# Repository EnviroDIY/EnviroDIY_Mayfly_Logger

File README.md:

EnviroDIY Mayfly Data Logger
==============
The [EnviroDIY™ Mayfly Data Logger](http://envirodiy.org/mayfly/) is an Arduino-framework microcontroller board designed specifically for environmental Internet of Things (IoT) applications with the goal to facilitate professional-quality, do-it-yourself (DIY) environmental science and monitoring.

This [EnviroDIY_Mayfly_Logger Github repository](https://github.com/EnviroDIY/EnviroDIY_Mayfly_Logger) provides hardware design files and example code sketches, the [EnviroDIY community](https://www.envirodiy.org) provides support via project posts and forums, and the [Mayfly Logger board is available for purchase on the [EnviroDIY Shop](https://www.envirodiy.org/shop/) for user convenience.

## Features:

- ATmega1284p processor
    - 128kB program (flash) memory, 16kB RAM
    - 2 UART, 1 I2C, 1 SPI connection
    - 32 total I/O pins
    - 3.3V, 8MHz operating frequency
- Integrated 6V solar lipo battery charger
- Precise real time clock (RTC, [DS3231](https://datasheets.maximintegrated.com/en/ds/DS3231.pdf)) with separate power supply
- Auxillary 16 bit ADC ([TI ADS1115](http://www.ti.com/lit/ds/symlink/ads1114.pdf))
- FTDI chip for USB communication via USB-C port
- microSD memory card socket
- XBee radio/wifi/cellular module socket
- 7 [Grove](http://wiki.seeedstudio.com/Grove_System/) connectors with access to I2C, auxillary ADC, and digital pins
- 0.5A switchable power supply for sensors at 3.3V and 5V, and 0.15A at 12V
- On-board power switch
- Two controllable LED's (red and green)
- One programmable push-button
- Onboard humidity/temperature sensor and analog light sensor
- Onboard auxiliary 8MB flash memory chip

## Pin-out for v1.x

| Pin Number[s] | Function             | Access                                 | Notes |
|---------------|----------------------|----------------------------------------|-------|
| D0/D1         | Serial Rx/Tx (UART)  | Connected to FTDI for USB programming  | Also accessible via programming port, 20 pin header, and XBee socket via SJ8/9 |
| D2/D3         | Serial1 Rx/Tx (UART) | XBee socket Din/Dout (pins 2/3)        | Also accessible via 20 pin header, can be disconnected from XBee socket via SJ8/9 |
| D19           | XBee CTS             | XBee socket CTS (pin 12)               | Also accessible via 20 pin header |
| D20           | XBee RTS             | XBee socket RTS (pin 16)               | Also accessible via 20 pin header |
| D23           | XBee DTR             | XBee socket DTR (pin 9)                | Also accessible via 20 pin header |
| A5=D29*       | XBee Assoc or RI     | XBee socket Assoc or RI (pin 15 or 20) | Not connected to XBee socket by default, use SJ7 to connect; Also accessible via 20 pin header |
| D16/D17       | I2C SCL/SDA ("Wire") | Grove connector                        | Also accessible via 20 pin header |
| D13/D14/D15   | SPI MOSI/MISO/SCK    | microSD card slot & SPI header         |  |
| D12           | microSD chip select  | microSD card slot & SPI header         |  |
| D18           | SD card detect OR RTC 32KHz | 20 pin header                   | Not connected to either SD or RTC by default, use SJ6 for RTC or SJ10 for SD, _do not use both_ |
| A7=D31 _or_ D10 | RTC Interrupt      | 20 pin header                          | A7 is connected to RTC interrupt by default; Use SJ1 to disconnect A7 and/or to connect D10 |
| D22           | Switched power/LED4  | Switched power on all Grove ports      | Pin is not directly accessible, only switched power; Cut SJ3 to disconnect LED4 (red) |
| D21           | user push button     | 20 pin header                          | Cut SJ to disconnect button |
| D8            | LED1 (green)         | 20 pin header                          |  |
| D9            | LED2 (red)           | 20 pin header                          |  |
| A6=D30        | Battery measurement  | None                                   | Connected via voltage divider |
| D4-7, D10-11  | General Purpose I/O  | Grove connector; 20 pin header         |  |
| AA0-AA3       | Auxilliary ADC       | Grove connector; 20 pin header         | Connected to _Auxillary_ adc (TI ADS1115), not to Mayfly analog pins |

## Solder Jumper Connections for v1.x

| Number | Function                        | Default Connection                |
|--------|---------------------------------|-----------------------------------|
| SJ1    | Connect to interrupt from RTC   | Pin A7 connected to RTC interrupt       |
| SJ2    | Disconnect D21 from user button | Pin D21 is connected to button (closed) |
| SJ3    | Disconnect D22 from LED3        | Pin D22 is connected to LED3 (closed)   |
| SJ4    | Disconnect LED4 from solar      | LED4 indicates solar charging status (closed) |
| SJ7    | Pin A5 to XBee ASSOC _or_ RI    | Not connected (all pads open)                 |
| SJ8    | XBee Din to TX0/TX1             | XBee Din connected to TX1                     |
| SJ9    | XBee Dout to RX0/RX1            | XBee Dout connected to RX1                    |
| SJ12   | D10 external pull-up            | D10 (INT2) is not pulled up externally (open) |

## Programming

Mayfly Data Logger can be programmed using standard Aruduino code and community libraries via the [Arduino Integrated Development Environment (IDE) software](https://www.arduino.cc/en/Main/Software) or the more powerful [PlatformIO](https://platformio.org) extensions for [Visual Studio Code](https://code.visualstudio.com/) or [Atom](https://atom.io/).

To use the Mayfly with the Arduino IDE you must add "EnviroDIY ATmega Boards" using the Tools > Board > Boards Manager as described in the [Mayfly Data Logger Software](http://envirodiy.org/mayfly/software/) post

No addition set-up is required to use the PlatformIO.
The proper enviroment settings for the Mayfly in a platformio.ini file are:

```ini
[env:mayfly]
platform = atmelavr
board = mayfly
framework = arduino
```

## Additional Resources and Links

- Read the [Getting Started With the Mayfly Data Logger](http://envirodiy.org/mayfly/) page on the EnviroDIY community website for guidance for beginners with the Mayfly, sensor station maintence, and data management.
- Make use of the [The EnviroDIY Mayfly Data l=Logger Forum](https://www.envirodiy.org/forum/mayfly-data-logger/) to ask and answer questions about the Mayfly
- Learn Mayfly basics following our [Mayfly Data Logger Software](http://envirodiy.org/mayfly/software/) post and running the example and workshop code sketches, using the Arduino IDE (from File > Sketchbook), from our [EnviroDIY_Mayfly_Logger > examples](https://github.com/EnviroDIY/EnviroDIY_Mayfly_Logger/tree/master/examples) or [EnviroDIY_Mayfly_Logger > workshop](https://github.com/EnviroDIY/EnviroDIY_Mayfly_Logger/tree/master/workshop) folders.
- Advance your capabilities to deploy solar-powered environmental monitoring stations with our [LearnEnviroDIY tutorial](https://envirodiy.github.io/LearnEnviroDIY/)
- Utilize the [ModularSensors](https://github.com/EnviroDIY/ModularSensors) code library and other [EnviroDIY libraries on GitHub](https://github.com/EnviroDIY) for datalogging built around the Mayfly
- Find and attend a training workshop for do-it-yourself environmental monitoring built around the Mayfly by contacting the Stroud Water Research Center's [citizen science outreach](https://stroudcenter.org/people/bressler/) or [education](https://stroudcenter.org/education/contact/) departments.

## Design Files & Further Documentation

We share our EnviroDIY Mayfly logger hardware design files and documentation in this repository's [Hardware Design Files](hardware) pages and [Documentation](doc) pages.

## License
Software sketches and code are released under the BSD 3-Clause License -- See [LICENSE.md](https://github.com/EnviroDIY/EnviroDIY_Mayfly_Logger/blob/master/LICENSE.md) file for details.

Documentation is licensed as [Creative Commons Attribution-ShareAlike 4.0](https://creativecommons.org/licenses/by-sa/4.0/) (CC-BY-SA) copyright.

Hardware designs shared are released, unless otherwise indicated, under the [CERN Open Hardware License 1.2](https://www.ohwr.org/projects/cernohl/wiki) (CERN_OHL).

## Credits
[EnviroDIY](http://envirodiy.org/)™ is presented by the Stroud Water Research Center, with contributions from a community of enthusiasts sharing do-it-yourself ideas for environmental science and monitoring.

[Shannon Hicks](https://github.com/s-hicks2) is the primary developer of the EnviroDIY Mayfly Data Logger hardware, with input from many [other contributors](https://github.com/EnviroDIY/EnviroDIY_Mayfly_Logger/graphs/contributors).

The Mayfly was developed based on the [SODAQ Mbili board](https://support.sodaq.com/sodaq-one/sodaq-mbili-1284p/) hardware and the [SODAQ Mbili bootloader](https://github.com/SodaqMoja/HardwareMbili) software, designed by Gregory Knauff (GKNFF).

This project has benefited from the support from the following funders:

* William Penn Foundation
* US Environmental Protection Agency (EPA)
* National Science Foundation, awards [EAR-0724971](http://www.nsf.gov/awardsearch/showAward?AWD_ID=0724971), [EAR-1331856](http://www.nsf.gov/awardsearch/showAward?AWD_ID=1331856), [ACI-1339834](http://www.nsf.gov/awardsearch/showAward?AWD_ID=1339834)
* Stroud Water Research Center endowment

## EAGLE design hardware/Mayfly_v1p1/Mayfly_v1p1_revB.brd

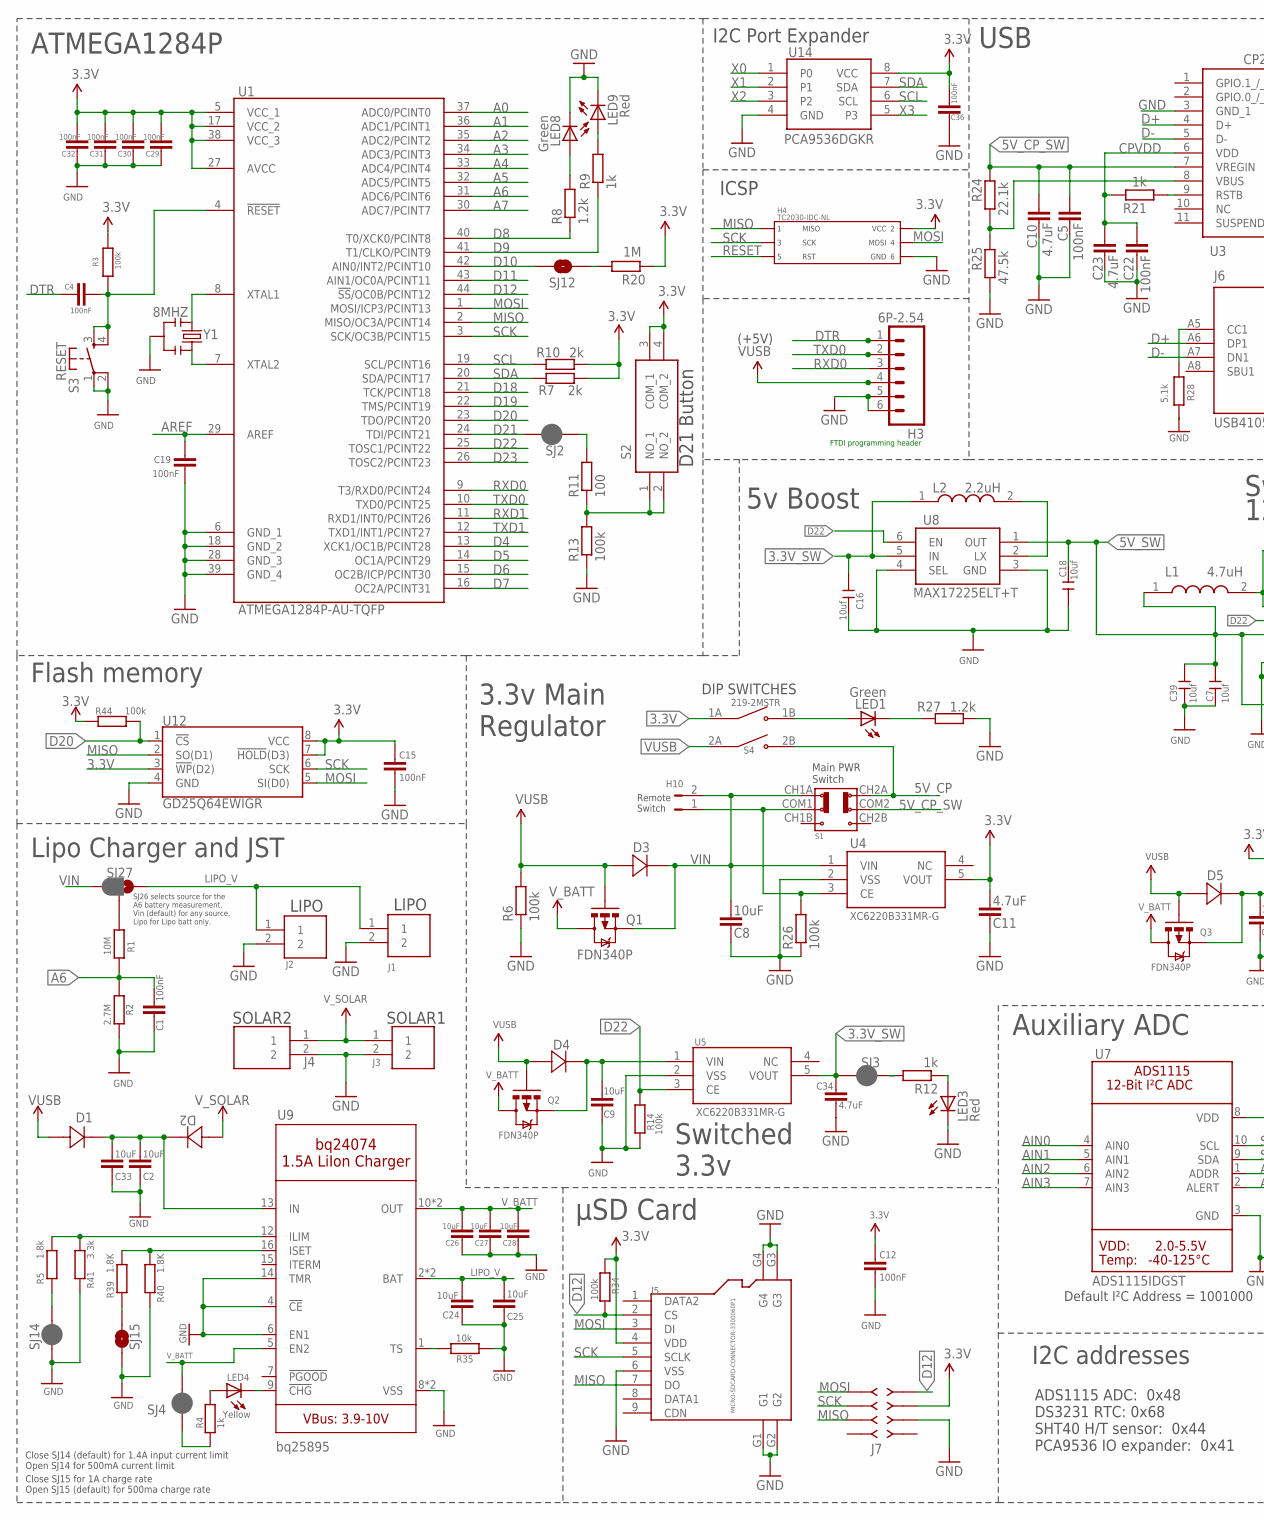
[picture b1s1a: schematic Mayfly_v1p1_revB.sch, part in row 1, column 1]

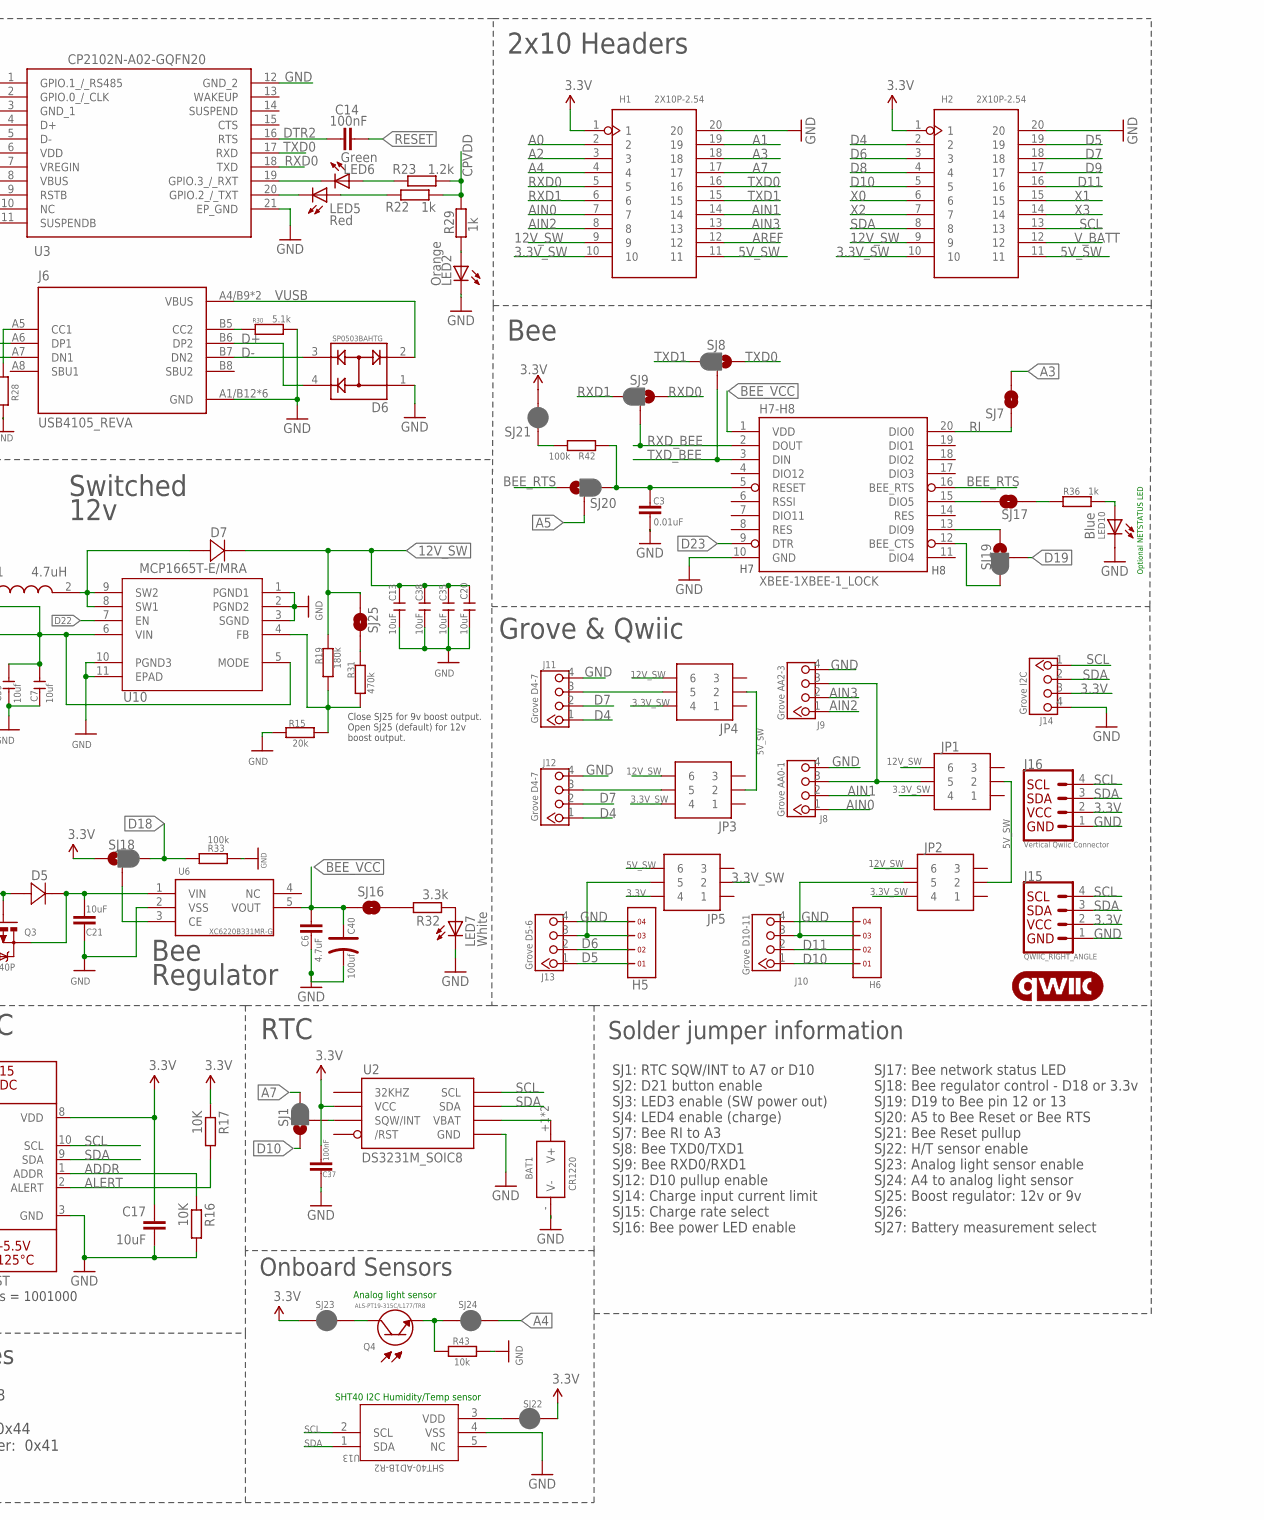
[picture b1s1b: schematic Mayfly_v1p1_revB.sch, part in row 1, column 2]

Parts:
BAT1: CR1220; BAT2P-13.5-CR1220
C1, C4, C5, C12, C14, C22, C29, C30, C31, C32, C36, C37: 100nF; C0603
C2, C8, C9, C17, C21, C24, C25, C26, C27, C28, C33: 10uF; C0603
C3: 0.01uF; C0603
C6, C10, C11, C23, C34: 4.7uF; C0603
C7, C39: 10uf; C0805
C13, C20, C35, C38: 10uF; C1206
C15, C19: 100nF; C0402
C16, C18: 10uf; C0603
C40: 100uf; AVX-B
D1, D2, D3, D4, D5, D7: MSS2P2-M3/89A; DIODE_MSP3V3
D6: SP0503BAHTG; SOT143
H1, H2: 2X10P-2.54; H2X10-2.54
H3: 6P-2.54; 1X06_FEMALE_LOCK.010
H4: TC2030-IDC-NL
H5, H6: 1X4
H7-H8: XBEE-1XBEE-1_LOCK; XBEE-1_LOCK
H10: JUMPER-PTH-2-NO; PTH-JUMPER-2-NO_NO_SILK
J1, J2, J3: JST_EPH_2PIN; JST_EPH_B2B-PH-K-S
J4: 1778557; SHDR2W70P0X250_1X2_670X500X765
J5: MICRO-SDCARD-CONNECTOR-3300060P1; 9P-SMD-W-RING
J6: USB4105_REVA; GCT_USB4105_REVA
J7: 79107-08_S; 79107-08
J8: Grove AA0-1; HW4-2.0
J9: Grove AA2-3; HW4-2.0
J10: Grove D10-11; HW4-2.0
J11, J12: Grove D4-7; HW4-2.0
J13: Grove D5-6; HW4-2.0
J14: Grove I2C; HW4-2.0
J15: QWIIC_RIGHT_ANGLE; JST04_1MM_RA
J16: Vertical Qwiic Connector; JST04_1MM_VERT
JP1, JP2, JP3, JP4, JP5: M22-2520305; HDRV6W50P200_2X3_600X400X525P
L1: 4.7uH; XAL4030472MEC
L2: 2.2uH; 1285ASH1R0MP2
LED1, LED6, LED8: Green; LED-0603
LED2: Orange; LED-0603
LED3, LED5, LED9: Red; LED-0603
LED4: Yellow; LED-0603
LED7: White; LED-0603
LED10: Blue; LED-0603
LOGO4: QWIIC_LOGO_5MM; QWIIC_5MM
Q1, Q2, Q3: FDN340P; SOT23-S-PADS
Q4: ALS-PT19-315C/L177/TR8; XDCR_ALS-PT19-315C/L177/TR8
R1: 10M; R0402
R2: 2.7M; R0402
R3, R26: 100k; R0603
R4, R9, R12, R21, R22, R29, R36: 1k; R0402
R5: 1.8k; R0402
R6, R13, R14, R33, R34, R42, R44: 100k; R0402
R7, R10: 2k; R0603
R8, R23, R27: 1.2k; R0402
R11: 100; R0402
R15: 20k; R0402
R16, R17: 10K; R0402
R19: 180k; R0402
R20: 1M; R0603
R24: 22.1k; R0402
R25: 47.5k; R0402
R28, R30: 5.1k; R0402
R31: 470k; R0402
R32, R41: 3.3k; R0402
R35, R43: 10k; R0402
R39, R40: 1.8K; R0402
S1: SWITCH-2CH-6P-3010010P1; 6P-2CH-2.54-9.1X3.5X3.2+2H
S2: PTS647SK38SMTR2LFS
S3: MOMENTARY-SWITCH-SPST-2-SMD-4.6X2.8MM; TACTILE_SWITCH_SMD_4.6X2.8MM
S4: 219-2MSTR; SW_219-2MSTR
SJ1, SJ8, SJ9, SJ18, SJ19, SJ20, SJ27: JUMPER-SMT_3_1-NC_PASTE_SILK; SMT-JUMPER_3_1-NC_PASTE_SILK
SJ2, SJ3, SJ4, SJ14, SJ21, SJ22, SJ23, SJ24: JUMPER-SMT_2_NC_PASTE_SILK; SMT-JUMPER_2_NC_PASTE_SILK
SJ7, SJ15, SJ16, SJ17, SJ25: JUMPER-SMT_2_NO_SILK; SMT-JUMPER_2_NO_SILK
SJ12: SOLDERJUMPERNO; SJ_2S-NO
U1: ATMEGA1284P-AU-TQFP; QFP80P1200X1200X120-44N
U2: DS3231M_SOIC8; SO8
U3: CP2102N-A02-GQFN20; CP2102NA02GQFN20
U4, U5, U6: XC6220B331MR-G; SOT95P280X130-5N
U7: ADS1115IDGST; MSOP10
U8: MAX17225ELT+T; MAX17225ELTT
U9: ADAFRUIT_POWER_BQ24074; ADAFRUIT_POWER_QFN16_3MM
U10: MCP1665T-E/MRA; QFN50P200X200X90-11N
U12: GD25Q64EWIGR; WSON8-6X5MM
U13: SHT40-AD1B-R2; SHT4X_SEN
U14: PCA9536DGKR; SOP65P490X110-8N
Y1: 8MHZ; X3-SMD-3.6X1.3X0.8MM

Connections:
3.3V: C11.2, C12.2, C15.2, C17.1, C29.2, C30.2, C31.2, C32.2, C36.2, C37.2, H1.1, H2.1, H4.P$2 (PIN2), J5.4 (VDD), J7.3, J14.3, J15.2, J16.2, JP5.4, R3.2, R7.1, R10.2, R17.1, R20.2, R34.1, R44.1, S2.3 (COM_1), S2.4 (COM_2), S4.1A (COM1), SJ18.1, SJ21.2, SJ22.1, SJ23.1, U1.5 (VCC_1), U1.17 (VCC_2), U1.27 (AVCC), U1.38 (VCC_3), U2.2 (VCC), U4.5 (VOUT), U7.8 (VDD), U12.3 (!WP!(D2)), U12.7 (!HOLD!(D3)), U12.8 (VCC), U14.8 (VCC)
3.3V_SW: C16.2, C34.2, H1.10, H2.10, JP1.4, JP2.4, JP3.4, JP4.4, JP5.2, L2.1, SJ3.1, U5.5 (VOUT), U8.5 (IN)
5V_CP: S1.CH2A, S4.2B (NO2)
5V_CP_SW: C5.2, C10.2, R24.2, S1.COM2, U3.7 (VREGIN)
5V_SW: C7.1, C18.1, C39.1, H1.11, H2.11, JP1.2, JP2.2, JP3.2, JP4.2, JP5.6, L1.1, U8.1 (OUT), U10.5 (MODE), U10.6 (VIN)
12V_SW: C13.2, C20.2, C35.2, C38.2, D7.1, H1.9, H2.9, JP1.6, JP2.6, JP3.6, JP4.6, R19.1, SJ25.2
A0: H1.2, U1.37 (ADC0/PCINT0)
A1: H1.19, U1.36 (ADC1/PCINT1)
A2: H1.3, U1.35 (ADC2/PCINT2)
A3: H1.18, SJ7.2, U1.34 (ADC3/PCINT3)
A4: H1.4, SJ24.2, U1.33 (ADC4/PCINT4)
A5: SJ20.2, U1.32 (ADC5/PCINT5)
A6: C1.2, R1.1, R2.2, U1.31 (ADC6/PCINT6)
A7: H1.17, SJ1.3, U1.30 (ADC7/PCINT7)
ADDR: R16.1, U7.1 (ADDR)
AIN0: H1.7, J8.1, U7.4 (AIN0)
AIN1: H1.14, J8.2, U7.5 (AIN1)
AIN2: H1.8, J9.1, U7.6 (AIN2)
AIN3: H1.13, J9.2, U7.7 (AIN3)
ALERT: R17.2, U7.2 (ALERT)
AREF: C19.2, H1.12, U1.29 (AREF)
BEE_RTS: H7-H8.16 (BEE_RTS), SJ20.1
BEE_VCC: C6.2, C40.+, H7-H8.1 (VDD), SJ16.1, U6.5 (VOUT)
BQ_IN: C2.2, C33.2, D1.1, D2.1, U9.13 (IN)
C: U1.8 (XTAL1), Y1.1
CPVDD: C22.2, C23.2, R21.2, R22.1, R23.1, R29.1, U3.6 (VDD)
C_N: U1.7 (XTAL2), Y1.3
D4: H2.2, J11.1, J12.1, U1.13 (XCK1/OC1B/PCINT28)
D5: H2.19, H5.1, J13.1, U1.14 (OC1A/PCINT29)
D6: H2.3, H5.2, J13.2, U1.15 (OC2B/ICP/PCINT30)
D7: H2.18, J11.2, J12.2, U1.16 (OC2A/PCINT31)
D8: H2.4, R8.1, U1.40 (T0/XCK0/PCINT8)
D9: H2.17, R9.1, U1.41 (T1/CLKO/PCINT9)
D10: H2.5, H6.1, J10.1, SJ1.1, SJ12.1, U1.42 (AIN0/INT2/PCINT10)
D11: H2.16, H6.2, J10.2, U1.43 (AIN1/OC0A/PCINT11)
D12: J5.2 (CS), J7.1, R34.2, U1.44 (!SS!/OC0B/PCINT12)
D18: R33.2, SJ18.3, U1.21 (TCK/PCINT18)
D19: SJ19.2, U1.22 (TMS/PCINT19)
D20: R44.2, U1.23 (TDO/PCINT20), U12.1 (!CS!)
D21: SJ2.2, U1.24 (TDI/PCINT21)
D22: R14.2, U1.25 (TOSC1/PCINT22), U5.3 (CE), U8.6 (EN), U10.7 (EN)
D23: H7-H8.9 (DTR), U1.26 (TOSC2/PCINT23)
D+: D6.4, J6.A6 (DP1), J6.B6 (DP2), U3.4 (D+)
D-: D6.3, J6.A7 (DN1), J6.B7 (DN2), U3.5 (D-)
DTR: C4.1, H3.1
DTR2: C14.2, U3.16 (RTS)
GND: BAT1.- (V-), C1.1, C2.1, C3.1, C5.1, C6.1, C7.2, C8.1, C9.1, C10.1, C11.1, C12.1, C13.1, C15.1, C16.1, C17.2, C18.2, C19.1, C20.1, C21.1, C22.1, C23.1, C24.1, C25.1, C26.1, C27.1, C28.1, C29.1, C30.1, C31.1, C32.1, C33.1, C34.1, C35.1, C36.1, C37.1, C38.1, C39.2, C40.-, D6.1, H1.20, H2.20, H3.5, H3.6, H4.P$6 (PIN6), H5.4, H6.4, H7-H8.10 (GND), J1.2, J2.2, J3.2, J4.2, J5.6 (VSS), J5.G1, J5.G2, J5.G3, J5.G4, J6.A1/B12 (GND), J6.B1/A12 (GND), J6.G1 (GND), J6.G2 (GND), J6.G3 (GND), J6.G4 (GND), J7.5, J8.4, J9.4, J10.4, J11.4, J12.4, J13.4, J14.4, J15.1, J16.1, LED2.C, LED3.C, LED7.C, LED8.C, LED9.C, LED10.C, R2.1, R6.1, R13.1, R14.1, R15.2, R16.2, R25.1, R26.1, R27.1, R28.2, R30.2, R33.1, R35.1, R40.1, R41.1, R43.2, S3.1, S3.2, SJ14.2, SJ15.1, U1.6 (GND_1), U1.18 (GND_2), U1.28 (GND_3), U1.39 (GND_4), U2.5 (GND), U3.3 (GND_1), U3.12 (GND_2), U3.21 (EP_GND), U4.2 (VSS), U5.2 (VSS), U6.2 (VSS), U7.3 (GND), U8.3 (GND), U8.4 (SEL), U9.4 (!CE), U9.6 (EN1), U9.8 (VSS), U9.14 (TMR), U9.THERMAL (VSS), U10.1 (PGND1), U10.2 (PGND2), U10.3 (SGND), U10.10 (PGND3), U10.11 (EPAD), U12.4 (GND), U13.4 (VSS), U14.4 (GND), Y1.2
LIPO_V: C24.2, C25.2, J1.1, J2.1, SJ27.1, U9.2 (BAT), U9.3 (BAT)
MISO: H4.P$1 (PIN1), J5.7 (DO), J7.6, U1.2 (MISO/OC3A/PCINT14), U12.2 (SO(D1))
MOSI: H4.P$4 (PIN4), J5.3 (DI), J7.2, U1.1 (MOSI/ICP3/PCINT13), U12.5 (SI(D0))
unnamed: R20.1, SJ12.2
unnamed: H10.1, R26.2, S1.COM1, U4.3 (CE)
unnamed: R12.2, SJ3.2
unnamed: LED3.A, R12.1
unnamed: R11.1, R13.2, S2.1 (NO_1), S2.2 (NO_2)
unnamed: J8.3, J9.3, JP1.5
unnamed: R21.1, U3.9 (RSTB)
unnamed: R1.2, SJ27.2
unnamed: SJ18.2, U6.3 (CE)
unnamed: SJ1.2, U2.3 (SQW/INT)
unnamed: J6.A5 (CC1), R28.1
unnamed: LED4.A, R4.2
unnamed: R39.1, SJ15.2
unnamed: H7-H8.13 (DIO9), SJ19.1
unnamed: R4.1, SJ4.2
unnamed: D7.2, L1.2, U10.8 (SW1), U10.9 (SW2)
unnamed: R5.1, SJ14.1
unnamed: R11.2, SJ2.1
unnamed: J11.3, JP4.5
unnamed: LED1.C, R27.2
unnamed: H7-H8.12 (BEE_CTS), SJ19.3
unnamed: C3.2, H7-H8.5 (RESET), R42.1, SJ20.3
unnamed: C9.2, D4.1, Q2.2 (S), U5.1 (VIN)
unnamed: R15.1, R19.2, R31.2, U10.4 (FB)
unnamed: H6.3, J10.3, JP2.5
unnamed: LED1.A, S4.1B (NO1)
unnamed: H7-H8.15 (DIO5), SJ17.2
unnamed: J6.B5 (CC2), R30.1
unnamed: LED5.C, U3.20 (GPIO.2_/_TXT)
unnamed: LED6.C, U3.19 (GPIO.3_/_RXT)
unnamed: LED5.A, R22.2
unnamed: LED6.A, R23.2
unnamed: LED2.A, R29.2
unnamed: LED9.A, R9.2
unnamed: BAT1.+1 (V+), BAT1.+2 (V+), U2.6 (VBAT)
unnamed: LED8.A, R8.2
unnamed: LED7.A, R32.1
unnamed: R32.2, SJ16.2
unnamed: C21.2, D5.1, Q3.2 (S), U6.1 (VIN)
unnamed: LED10.A, R36.2
unnamed: R35.2, U9.1 (TS)
unnamed: LED4.C, U9.9 (!CHG)
unnamed: R42.2, SJ21.1
unnamed: R5.2, R41.2, U9.12 (ILIM)
unnamed: R39.2, R40.2, U9.16 (ISET)
unnamed: R36.1, SJ17.1
unnamed: SJ22.2, U13.3 (VDD)
unnamed: Q4.2 (E), R43.1, SJ24.1
unnamed: Q4.1 (C), SJ23.2
unnamed: H5.3, J13.3, JP5.5
unnamed: L2.2, U8.2 (LX)
unnamed: J12.3, JP3.5
unnamed: R31.1, SJ25.1
RESET: C4.2, C14.1, H4.P$5 (PIN5), R3.1, S3.3, S3.4, U1.4 (!RESET)
RI: H7-H8.20 (DIO0), SJ7.1
RXD0: H1.5, H3.3, SJ9.1, U1.9 (T3/RXD0/PCINT24), U3.18 (TXD)
RXD1: H1.6, SJ9.3, U1.11 (RXD1/INT0/PCINT26)
RXD_BEE: H7-H8.2 (DOUT), SJ9.2
SCK: H4.P$3 (PIN3), J5.5 (SCLK), J7.4, U1.3 (SCK/OC3B/PCINT15), U12.6 (SCK)
SCL: H2.13, J14.1, J15.4, J16.4, R10.1, U1.19 (SCL/PCINT16), U2.8 (SCL), U7.10 (SCL), U13.2 (SCL), U14.6 (SCL)
SDA: H2.8, J14.2, J15.3, J16.3, R7.2, U1.20 (SDA/PCINT17), U2.7 (SDA), U7.9 (SDA), U13.1 (SDA), U14.7 (SDA)
TXD0: H1.16, H3.2, SJ8.1, U1.10 (TXD0/PCINT25), U3.17 (RXD)
TXD1: H1.15, SJ8.3, U1.12 (TXD1/INT1/PCINT27)
TXD_BEE: H7-H8.3 (DIN), SJ8.2
VBS: R24.1, R25.2, U3.8 (VBUS)
VIN: C8.2, D3.1, H10.2, Q1.2 (S), S1.CH1A, SJ27.3, U4.1 (VIN)
VUSB: D1.2, D3.2, D4.2, D5.2, D6.2, H3.4, J6.A4/B9 (VBUS), J6.B4/A9 (VBUS), Q1.1 (G), Q2.1 (G), Q3.1 (G), R6.2, S4.2A (COM2)
V_BATT: C26.2, C27.2, C28.2, H2.12, Q1.3 (D), Q2.3 (D), Q3.3 (D), SJ4.1, U9.5 (EN2), U9.10 (OUT), U9.11 (OUT)
V_SOLAR: D2.2, J3.1, J4.1
X0: H2.6, U14.1 (P0)
X1: H2.15, U14.2 (P1)
X2: H2.7, U14.3 (P2)
X3: H2.14, U14.5 (P3)

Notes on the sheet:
ATMEGA1284P
Bee
Lipo Charger and JST
RTC
SOLAR1
LIPO
3.3v Main Regulator
(+5V)
USB
µSD Card
ICSP
Auxiliary ADC
Default I²C Address = 1001000
2x10 Headers
D21 Button
Close SJ14 (default) for 1.4A input current limit Open SJ14 for 500mA current limit
Close SJ15 for 1A charge rate Open SJ15 (default) for 500ma charge rate
SOLAR2
SHT40 I2C Humidity/Temp sensor
Analog light sensor
Switched 3.3v
Bee Regulator
Onboard Sensors
DIP SWITCHES
Remote Switch
Main PWR Switch
Optional NETSTATUS LED
Grove & Qwiic
FTDI programming header
I2C Port Expander
Switched 12v
5v Boost
Flash memory
Solder jumper information
SJ1: RTC SQW/INT to A7 or D10 SJ2: D21 button enable SJ3: LED3 enable (SW power out) SJ4: LED4 enable (charge) SJ7: Bee RI to A3 SJ8: Bee TXD0/TXD1 SJ9: Bee RXD0/RXD1 SJ12: D10 pullup enable SJ14: Charge input current limit SJ15: Charge rate select SJ16: Bee power LED enable
SJ17: Bee network status LED SJ18: Bee regulator control - D18 or 3.3v SJ19: D19 to Bee pin 12 or 13 SJ20: A5 to Bee Reset or Bee RTS SJ21: Bee Reset pullup SJ22: H/T sensor enable SJ23: Analog light sensor enable SJ24: A4 to analog light sensor SJ25: Boost regulator: 12v or 9v SJ26: SJ27: Battery 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
I2C addresses
ADS1115 ADC: 0x48 DS3231 RTC: 0x68 SHT40 H/T sensor: 0x44 PCA9536 IO expander: 0x41
Close SJ25 for 9v boost output. Open SJ25 (default) for 12v boost output.
SJ26 selects source for the A6 battery measurement. Vin (default) for any source. Lipo for Lipo batt only.

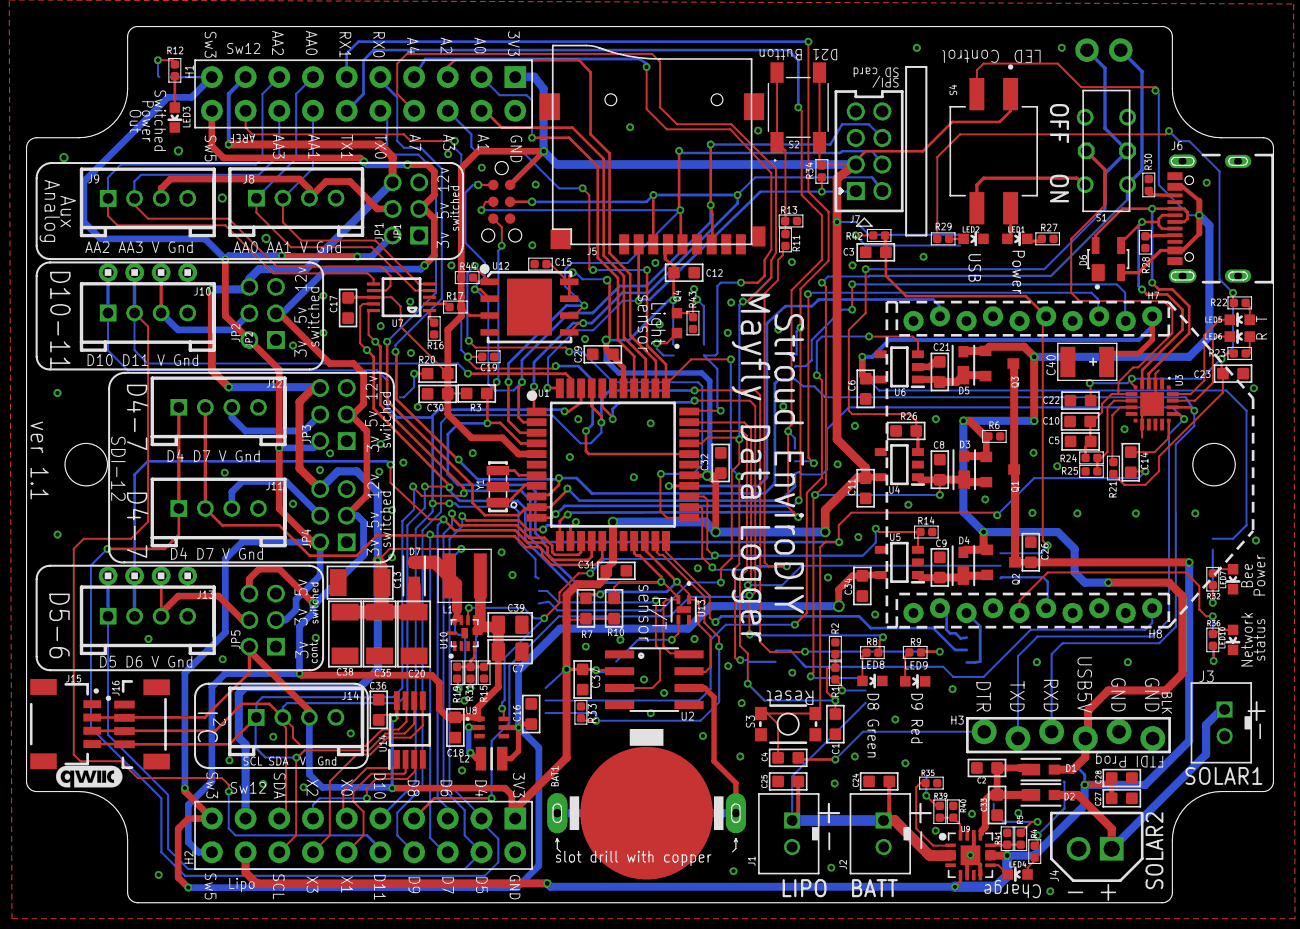
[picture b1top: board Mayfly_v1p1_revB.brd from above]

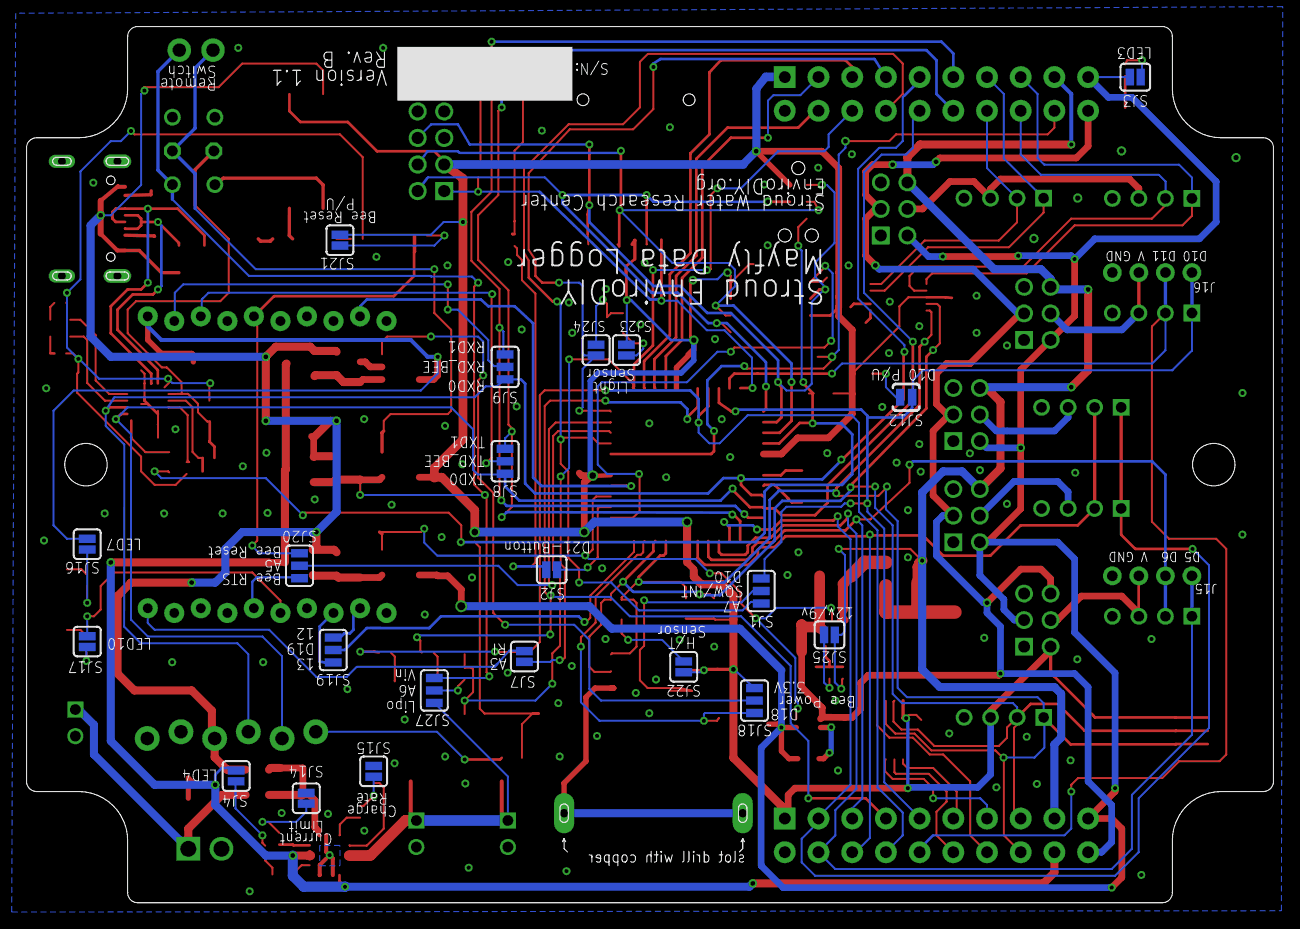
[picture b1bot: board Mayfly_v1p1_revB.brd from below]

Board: 4 copper layers, 94.0 x 66.0 mm, 174 parts (21 on the bottom side), 123 nets.

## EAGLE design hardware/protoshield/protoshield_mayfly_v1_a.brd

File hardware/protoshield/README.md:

EagleCAD files for the Mayfly Protoshield v1 (discontinued in 2020)

NOTE:  This ProtoShield is only compatible with the older Mayfly v0.5b boards.  It is not compatible with the newer Mayfly v1.0 or v1.1 board due to changes in the pinouts of the headers.  Do not attempt to use this ProtoShield with a Mayfly v1.0 or v1.1 board or damage to the Mayfly and/or ProtoShield will occur.

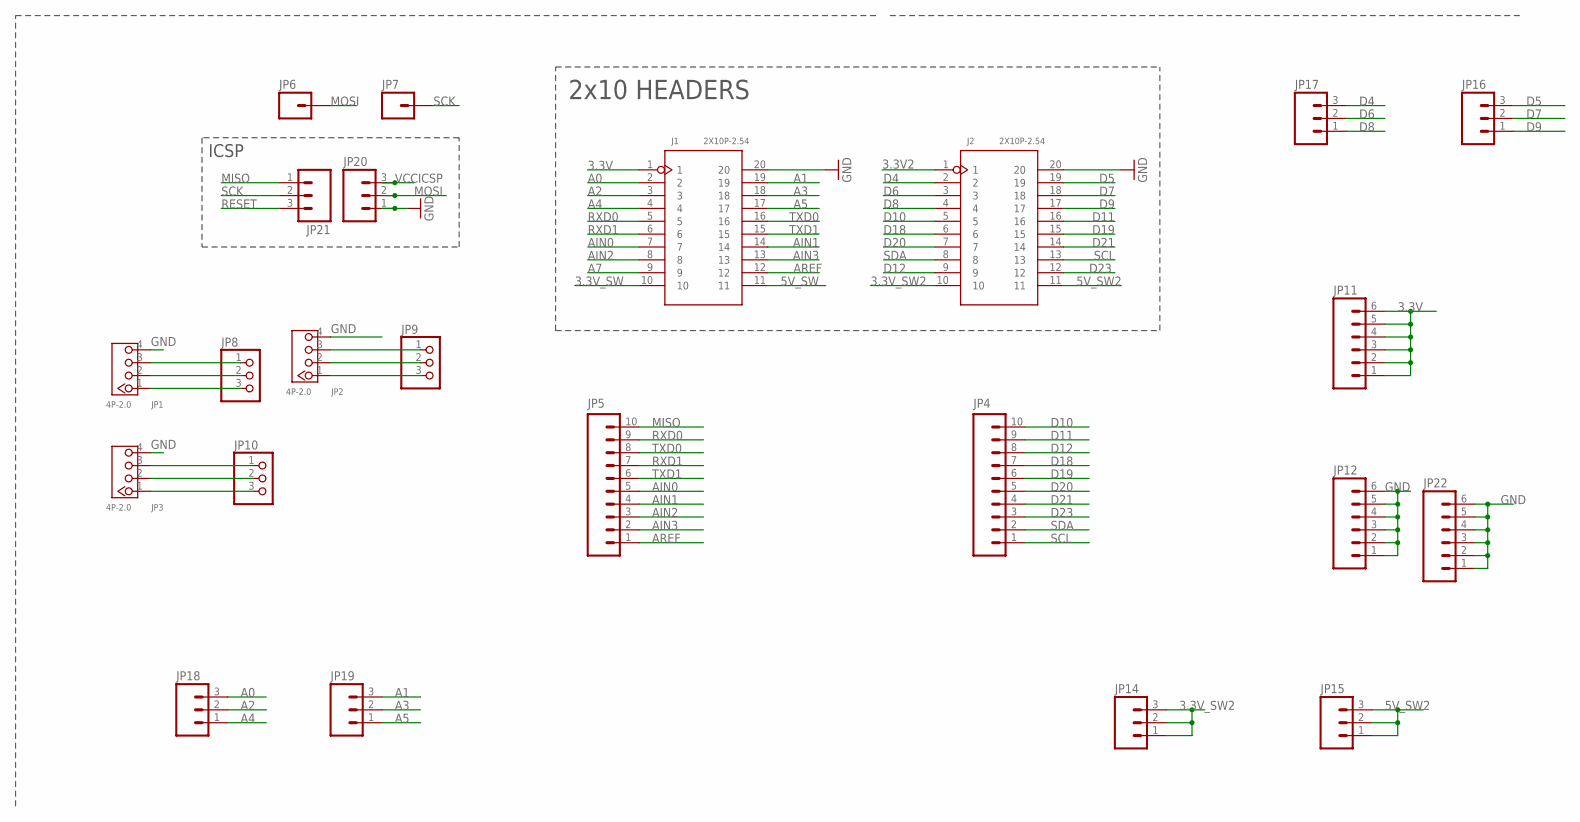
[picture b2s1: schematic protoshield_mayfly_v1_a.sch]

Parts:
J1, J2: 2X10P-2.54; H2X10-2.54
JP1, JP2, JP3: 4P-2.0; HW4-2.0
JP4, JP5: M10NO_SILK_PTH_FEMALE; 1X10_NO_SILK
JP6, JP7: M01PTH_NO_SILK_YES_STOP; 1X01_NO_SILK
JP8, JP9, JP10: PINHD-1X3CB; 1X03-CLEANBIG
JP11: M06NO_SILK_FEMALE_PTH; 1X06_NO_SILK
JP12, JP22: M06NO_SILK_YES_STOP; 1X06_NO_SILK_YES_STOP
JP14, JP15, JP16, JP17, JP18, JP19, JP20, JP21: M031X03_NO_SILK; 1X03_NO_SILK

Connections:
3.3V: J1.1, JP11.1, JP11.2, JP11.3, JP11.4, JP11.5, JP11.6
3.3V2: J2.1
3.3V_SW: J1.10
3.3V_SW2: J2.10, JP14.1, JP14.2, JP14.3
5V_SW: J1.11
5V_SW2: J2.11, JP15.1, JP15.2, JP15.3
A0: J1.2, JP18.3
A1: J1.19, JP19.3
A2: J1.3, JP18.2
A3: J1.18, JP19.2
A4: J1.4, JP18.1
A5: J1.17, JP19.1
A7: J1.9
AIN0: J1.7, JP5.5
AIN1: J1.14, JP5.4
AIN2: J1.8, JP5.3
AIN3: J1.13, JP5.2
AREF: J1.12, JP5.1
D4: J2.2, JP17.3
D5: J2.19, JP16.3
D6: J2.3, JP17.2
D7: J2.18, JP16.2
D8: J2.4, JP17.1
D9: J2.17, JP16.1
D10: J2.5, JP4.10
D11: J2.16, JP4.9
D12: J2.9, JP4.8
D18: J2.6, JP4.7
D19: J2.15, JP4.6
D20: J2.7, JP4.5
D21: J2.14, JP4.4
D23: J2.12, JP4.3
GND: J1.20, J2.20, JP1.4, JP2.4, JP3.4, JP12.1, JP12.2, JP12.3, JP12.4, JP12.5, JP12.6, JP20.1, JP22.1, JP22.2, JP22.3, JP22.4, JP22.5, JP22.6
MISO: JP5.10, JP21.1
MOSI: JP6.1, JP20.2
unnamed: JP1.1, JP8.3
unnamed: JP1.2, JP8.2
unnamed: JP1.3, JP8.1
unnamed: JP3.1, JP10.3
unnamed: JP3.2, JP10.2
unnamed: JP3.3, JP10.1
unnamed: JP2.3, JP9.1
unnamed: JP2.1, JP9.3
unnamed: JP2.2, JP9.2
RESET: JP21.3
RXD0: J1.5, JP5.9
RXD1: J1.6, JP5.7
SCK: JP7.1, JP21.2
SCL: J2.13, JP4.1
SDA: J2.8, JP4.2
TXD0: J1.16, JP5.8
TXD1: J1.15, JP5.6
VCCICSP: JP20.3

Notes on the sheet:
ICSP
2x10 HEADERS

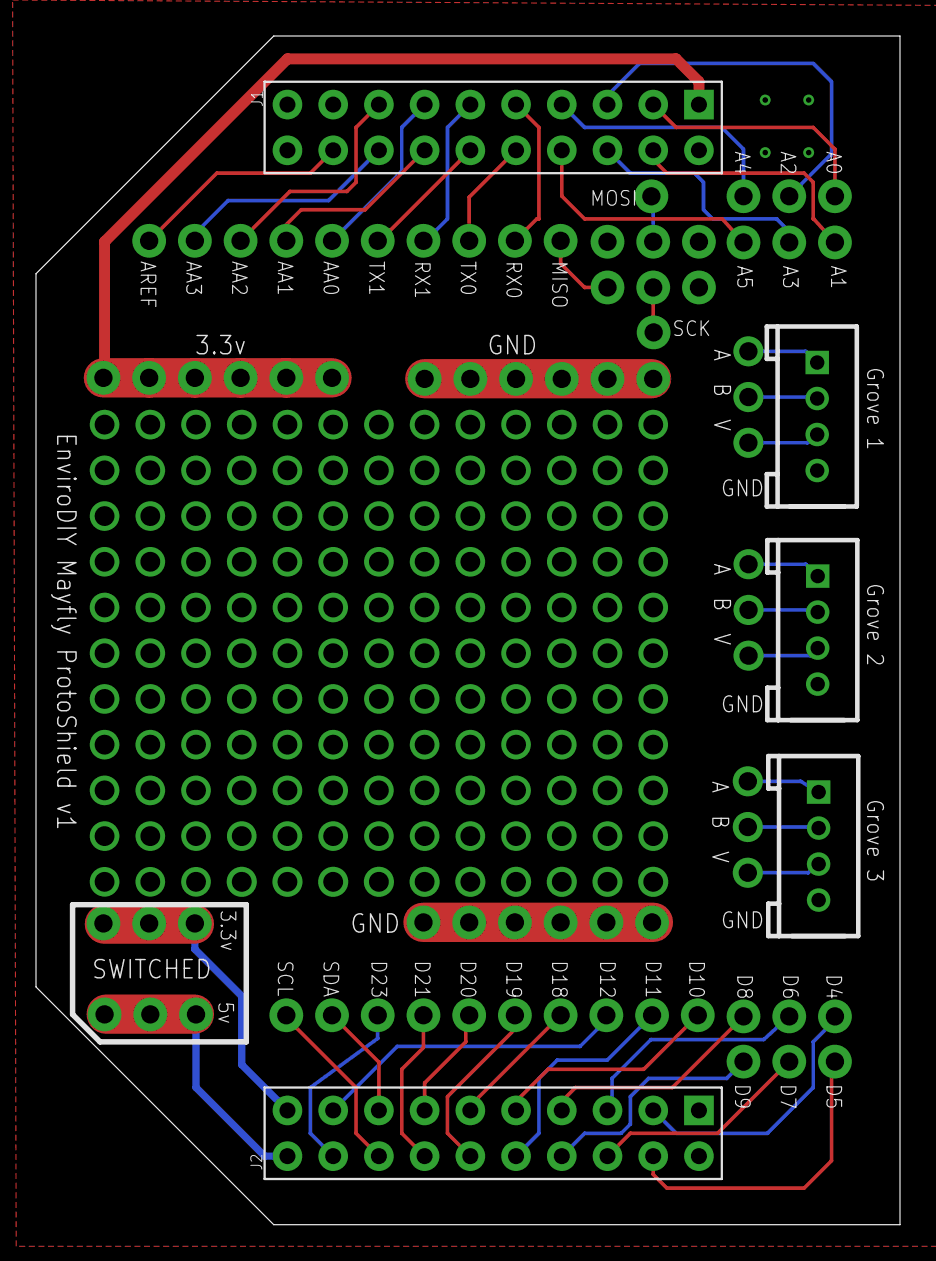
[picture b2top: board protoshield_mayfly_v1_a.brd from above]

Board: 2 copper layers, 48.0 x 66.0 mm, 23 parts (0 on the bottom side), 47 nets.

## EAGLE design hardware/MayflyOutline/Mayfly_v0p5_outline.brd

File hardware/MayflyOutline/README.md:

EagleCAD file for basic ouline of the Mayfly board with headers (v0.3, v0.4, v0.5, v0.5b)

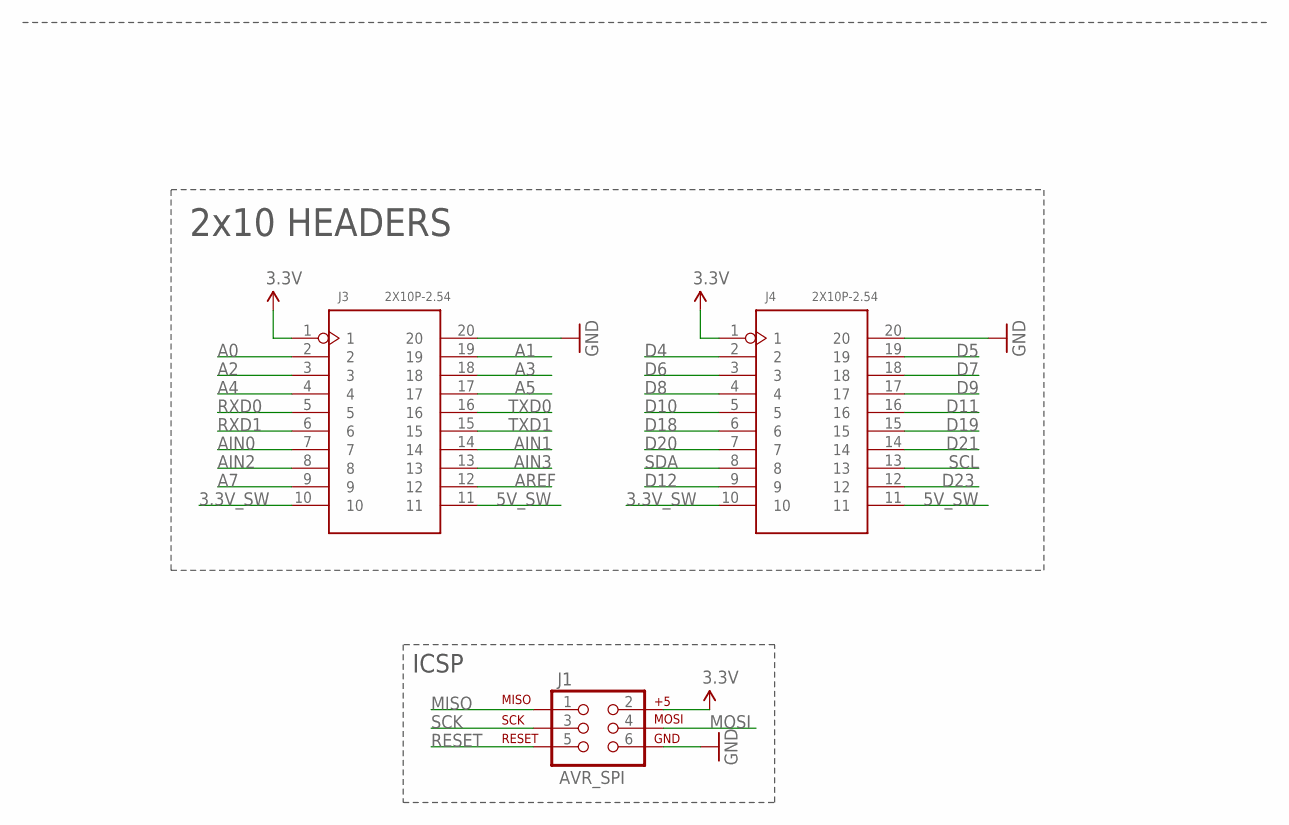
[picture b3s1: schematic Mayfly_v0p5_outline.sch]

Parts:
J1: AVR_SPI; 2X3-NS
J3, J4: 2X10P-2.54; H2X10-2.54

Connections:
3.3V: J1.2, J3.1, J4.1
3.3V_SW: J3.10, J4.10
5V_SW: J3.11, J4.11
A0: J3.2
A1: J3.19
A2: J3.3
A3: J3.18
A4: J3.4
A5: J3.17
A7: J3.9
AIN0: J3.7
AIN1: J3.14
AIN2: J3.8
AIN3: J3.13
AREF: J3.12
D4: J4.2
D5: J4.19
D6: J4.3
D7: J4.18
D8: J4.4
D9: J4.17
D10: J4.5
D11: J4.16
D12: J4.9
D18: J4.6
D19: J4.15
D20: J4.7
D21: J4.14
D23: J4.12
GND: J1.6, J3.20, J4.20
MISO: J1.1
MOSI: J1.4
RESET: J1.5
RXD0: J3.5
RXD1: J3.6
SCK: J1.3
SCL: J4.13
SDA: J4.8
TXD0: J3.16
TXD1: J3.15

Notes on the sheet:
ICSP
2x10 HEADERS

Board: 4 copper layers, 3 parts (0 on the bottom side), 4 nets, no tracks yet.

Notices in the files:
parts and their libraries:
SparkFun-Connectors: Licensing: CC v3.0 Share-Alike You are welcome to use this library for commercial purposes.
con-molex-milli-grid: Copyright (C) 2010, Bob Starr
SparkFun-Electromechanical: Licensing: Creative Commons ShareAlike 4.0 International - https://creativecommons.org/licenses/by-sa/4.0
